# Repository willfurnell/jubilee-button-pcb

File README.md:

# jubilee-button-pcb

PCB for the Jubilee Line button replacement PCB

Created using KiCad

Check out some sample code here: https://github.com/willfurnell/jubilee-hue

You should be able to send this straight off to JLCPCB if you want one - or contact me as I did a bulk order and may have some to post out!

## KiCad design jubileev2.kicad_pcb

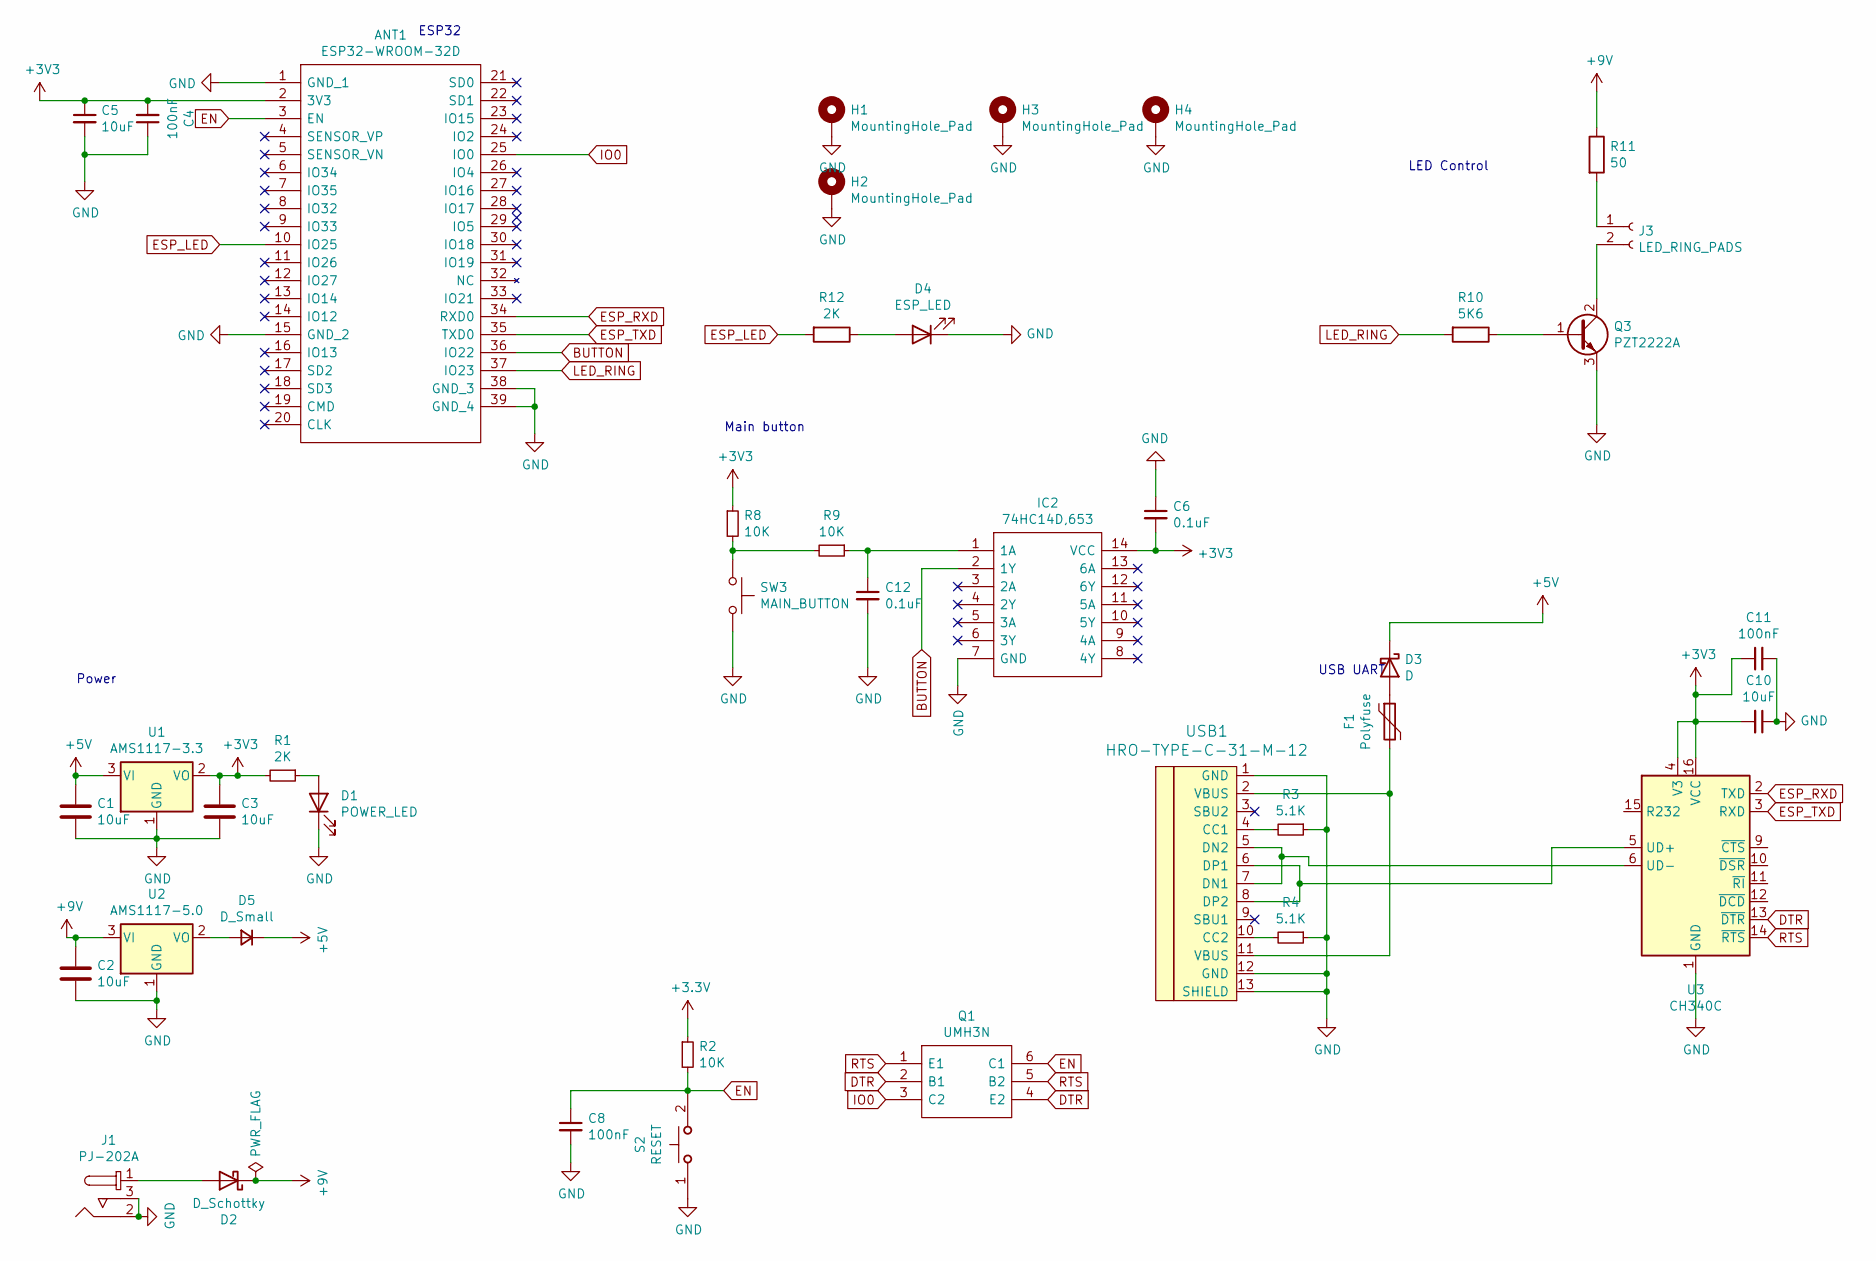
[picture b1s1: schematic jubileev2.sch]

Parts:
ANT1: ESP32-WROOM-32D; ESP32WROOM32D; Manufacturer_Part_Number ESP32-WROOM-32D; Mouser Part Number N/A
C1, C2, C3, C5, C10: 10uF; C_0805_2012Metric
C4, C8, C11: 100nF; C_0805_2012Metric
C6, C12: 0.1uF; C_0805_2012Metric
D1: POWER_LED; LED_0805_2012Metric
D2: D_Schottky; D_SOD-123
D3: D; D_SOD-123
D4: ESP_LED; LED_0805_2012Metric
D5: D_Small; D_SOD-123
F1: Polyfuse; Fuse_1206_3216Metric
H1, H2, H3, H4: MountingHole_Pad; MountingHole_3.5mm_Pad_TopBottom
IC2: 74HC14D,653; SOIC127P600X175-14N; Manufacturer_Part_Number 74HC14D,653; Mouser Part Number 771-74HC14D-T
J1: PJ-202A; Barrel_Jack_5.5mmODx2.1mmID_PJ-202A; MPN PJ-202A; Digi-Key_PN CP-202A-ND
J3: LED_RING_PADS; SolderWire-0.5sqmm_1x02_P4.6mm_D0.9mm_OD2.1mm
Q1: UMH3N; SOT65P230X110-6N; Manufacturer_Part_Number UMH3N
Q3: PZT2222A; SOT-223-3_TabPin2
R1, R12: 2K; R_0805_2012Metric
R2, R8, R9: 10K; R_0805_2012Metric
R3, R4: 5.1K; R_0805_2012Metric
R10: 5K6; R_0805_2012Metric
R11: 50; R_0805_2012Metric
S2: RESET; FSM2JRT; Mouser Part Number 506-FSM2JRT
SW3: MAIN_BUTTON; SolderWire-0.5sqmm_1x02_P4.6mm_D0.9mm_OD2.1mm
U1: AMS1117-3.3; SOT-223-3_TabPin2
U2: AMS1117-5.0; SOT-223-3_TabPin2
U3: CH340C; SOIC-16_3.9x9.9mm_P1.27mm
USB1: HRO-TYPE-C-31-M-12

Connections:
+5V: C1.1, D3.1 (K), D5.1 (K), U1.3 (VI)
+9V: C2.1, D2.1 (K), R11.1, U2.3 (VI)
BUTTON: ANT1.36 (IO22), IC2.2 (1Y)
DTR: Q1.2 (B1), Q1.4 (E2), U3.13 (~DTR)
EN: ANT1.3 (EN), C8.1, Q1.6 (C1), R2.2, S2.2
ESP_LED: ANT1.10 (IO25), R12.2
ESP_RXD: ANT1.34 (RXD0), U3.2 (TXD)
ESP_TXD: ANT1.35 (TXD0), U3.3 (RXD)
GND: ANT1.1 (GND_1), ANT1.15 (GND_2), ANT1.38 (GND_3), ANT1.39 (GND_4), C1.2, C2.2, C3.2, C4.1, C5.2, C6.1, C8.2, C10.1, C11.2, C12.2, D1.1 (K), D4.1 (K), H1.1, H2.1, H3.1, H4.1, IC2.7 (GND), J1.2, J1.3, Q3.3 (E), R3.1, R4.1, S2.1, SW3.2, U1.1 (GND), U2.1 (GND), U3.1 (GND), USB1.1 (GND), USB1.12 (GND), USB1.13 (SHIELD)
IO0: ANT1.25 (IO0), Q1.3 (C2)
LED_RING: ANT1.37 (IO23), R10.2
unnamed: C12.1, IC2.1 (1A), R9.1
unnamed: D1.2 (A), R1.1
unnamed: D2.2 (A), J1.1
unnamed: D3.2 (A), F1.1
unnamed: D4.2 (A), R12.1
unnamed: D5.2 (A), U2.2 (VO)
unnamed: F1.2, USB1.2 (VBUS), USB1.11 (VBUS)
unnamed: J3.1, R11.2
unnamed: J3.2, Q3.2 (C)
unnamed: Q3.1 (B), R10.1
unnamed: R3.2, USB1.4 (CC1)
unnamed: R4.2, USB1.10 (CC2)
unnamed: R8.2, R9.2, SW3.1
unnamed: U3.5 (UD+), USB1.6 (DP1), USB1.8 (DP2)
unnamed: U3.6 (UD-), USB1.5 (DN2), USB1.7 (DN1)
RTS: Q1.1 (E1), Q1.5 (B2), U3.14 (~RTS)

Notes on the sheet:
USB UART
Power
Main button
LED Control
ESP32

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
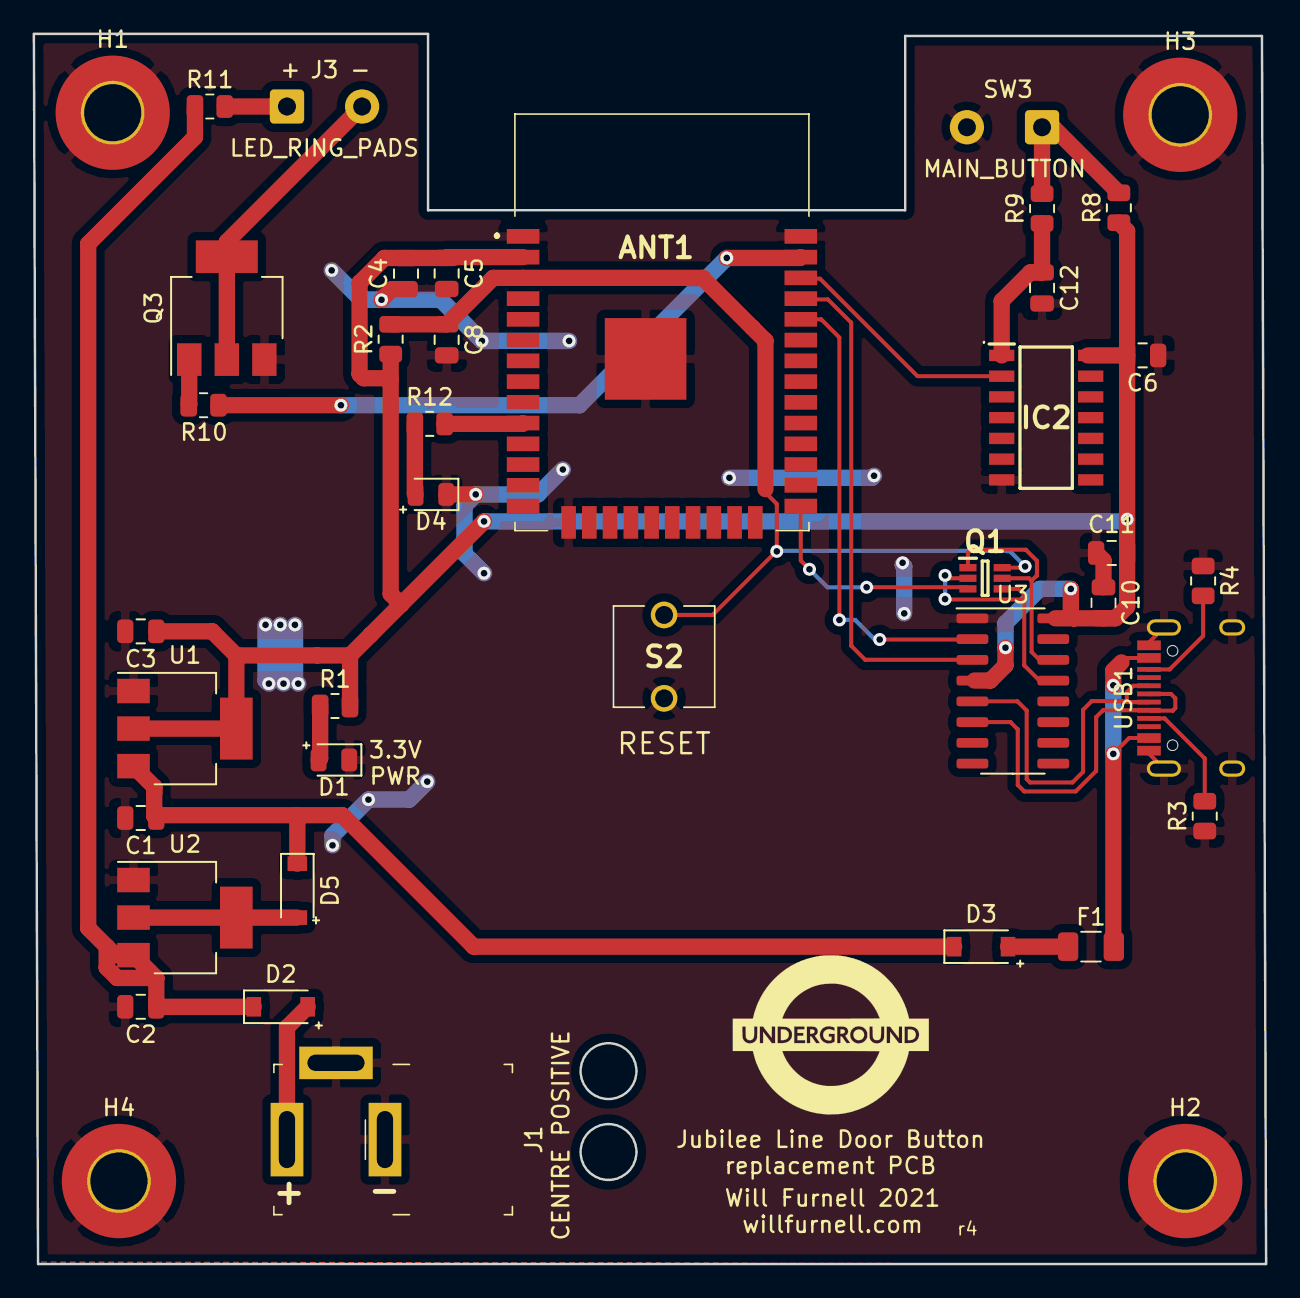
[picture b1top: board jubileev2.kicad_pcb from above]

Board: 2 copper layers, 75.4 x 75.3 mm, 41 parts (0 on the bottom side), 28 nets.

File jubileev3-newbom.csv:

"Id";"Designator";"Package";"Quantity";"Designation";"Supplier and ref";
1;"R3";"R_0805_2012Metric";1;"4.7K";;;
2;"IC1";"QFN50P400X400X80-25N-D";1;"CP2104-F03-GMR";;;
3;"C11,C3,C2,C1,C5";"C_0805_2012Metric";5;"10uF";;;
4;"C7";"R_0805_2012Metric";1;"0.1uF";;;
5;"H4,H3,H2,H1";"MountingHole_3.5mm_Pad_TopBottom";4;"MountingHole_Pad";;;
6;"C6,C4,C10,C9,C8,C12";"C_0805_2012Metric";6;"0.1uF";;;
7;"ANT1";"ESP32WROOM32D";1;"ESP32-WROOM-32D";;;
8;"IC2";"SOIC127P600X175-14N";1;"74HC14D,653";;;
9;"R12";"R_0805_2012Metric";1;"100R";;;
10;"D4";"LED_0805_2012Metric";1;"ESP_LED";;;
11;"S2";"FSM2JRT";1;"RESET";;;
12;"S1";"FSM2JRT";1;"BOOT";;;
13;"J1";"Barrel_Jack_5.5mmODx2.1mmID_PJ-202A";1;"PJ-202A";;;
14;"R2,R4,R5,R8,R9";"R_0805_2012Metric";5;"10K";;;
15;"F1";"Fuse_1206_3216Metric";1;"Polyfuse";;;
16;"G***";"roundel_ss";1;"LOGO";;;
17;"D5";"D_SOD-123";1;"D_Small";;;
18;"D3";"D_SOD-123";1;"D";;;
19;"D2";"D_SOD-123";1;"D_Schottky";;;
20;"D1";"LED_0805_2012Metric";1;"POWER_LED";;;
21;"J2";"USB_Micro-B_Amphenol_10118194_Horizontal";1;"USB_B_Micro";;;
22;"J3";"SolderWire-0.5sqmm_1x02_P4.6mm_D0.9mm_OD2.1mm";1;"LED_RING_PADS";;;
23;"Q1,Q2";"SOT-23";2;"MMBT3904";;;
24;"Q3";"SOT-223-3_TabPin2";1;"PZT2222A";;;
25;"R1";"R_0805_2012Metric";1;"1K";;;
26;"R10";"R_0805_2012Metric";1;"5K6";;;
27;"R11";"R_0805_2012Metric";1;"50";;;
28;"SW3";"SolderWire-0.5sqmm_1x02_P4.6mm_D0.9mm_OD2.1mm";1;"MAIN_BUTTON";;;
29;"U1";"SOT-223-3_TabPin2";1;"AMS1117-3.3";;;
30;"U2";"SOT-223-3_TabPin2";1;"AMS1117-5.0";;;

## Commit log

2021-09-19 Update schematic PDF
2021-09-19 Create LICENSE
